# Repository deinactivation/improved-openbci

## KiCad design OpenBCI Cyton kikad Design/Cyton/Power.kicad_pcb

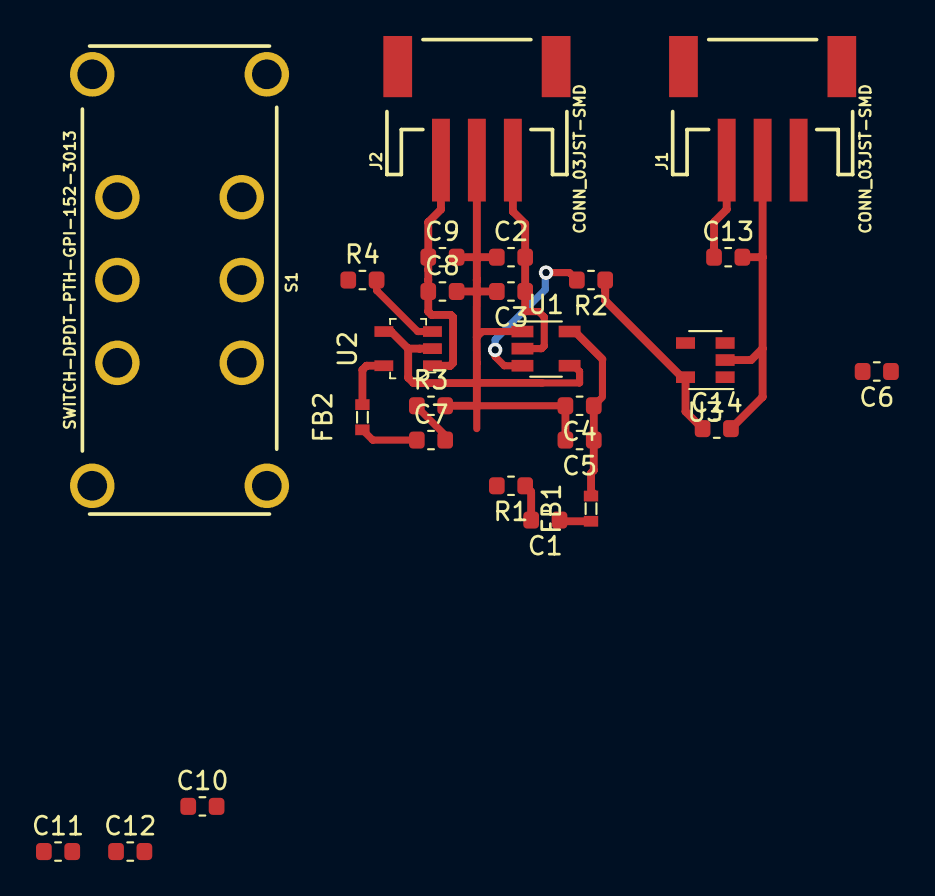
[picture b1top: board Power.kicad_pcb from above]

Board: 2 copper layers, 26 parts (0 on the bottom side), 15 nets.

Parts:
C1, C5, C7, C11: 10uF; C_0603_1608Metric
C2, C3, C4, C6, C8, C9, C10, C12, C13, C14: 2.2uF; C_0603_1608Metric
FB1, FB2: Ferrite_Bead_Small; 0603
J1, J2: CONN_03JST-SMD; JST-3-SMD
R1, R2, R3, R4: 10K; R_0603_1608Metric
S1: SWITCH-DPDT-PTH-GPI-152-3013; SWITCH_DPDT_PTH_GPI-152-3013
U1: ADP7182AUZJ; TSOT-23-5
U2: LP5907-SOT-23 2.5V; SOT-753
U3: MCP1754; SOT-23-5

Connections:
/3V: C13.1, J1.1, S1.10, S1.11, U3.1
/+2.5: C7.1, FB2.1
/+3V_IN: C8.1, C9.1, J2.1, U2.1
/-2.5: C1.1, FB1.1
/-3V_IN: C2.2, C3.1, J2.3, U1.2
/AnalogGround: C2.1, C3.2, C4.2, C5.2, C6.1, C8.2, C9.2, C10.2, C11.2, C12.1, J2.2, R1.2, R3.2, U1.1, U1.4, U2.2, U2.4
/Digital3V3: C14.1, R2.1, R4.1, U3.5
/DigitalGround: C13.2, C14.2, J1.2, S1.20, S1.21, U3.2
/Digital_Enable: S1.C@1, S1.C@2, U3.3
unnamed: C1.2, R1.1
unnamed: C4.1, C5.1, FB1.2, U1.5
unnamed: C6.2, R2.2, U1.3
unnamed: C7.2, R3.1
unnamed: C10.1, C11.1, FB2.2, U2.5
unnamed: C12.2, R4.2, U2.3

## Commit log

2019-02-24 Initial commit. No usable changes, but the start of a kikcad version of the cyton board.
2019-07-20 in-progress designs
